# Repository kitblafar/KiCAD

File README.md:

# KiCAD
KiCAD Projetcs at Work and at home

## Includes
- Test 141: A manufacturing test board

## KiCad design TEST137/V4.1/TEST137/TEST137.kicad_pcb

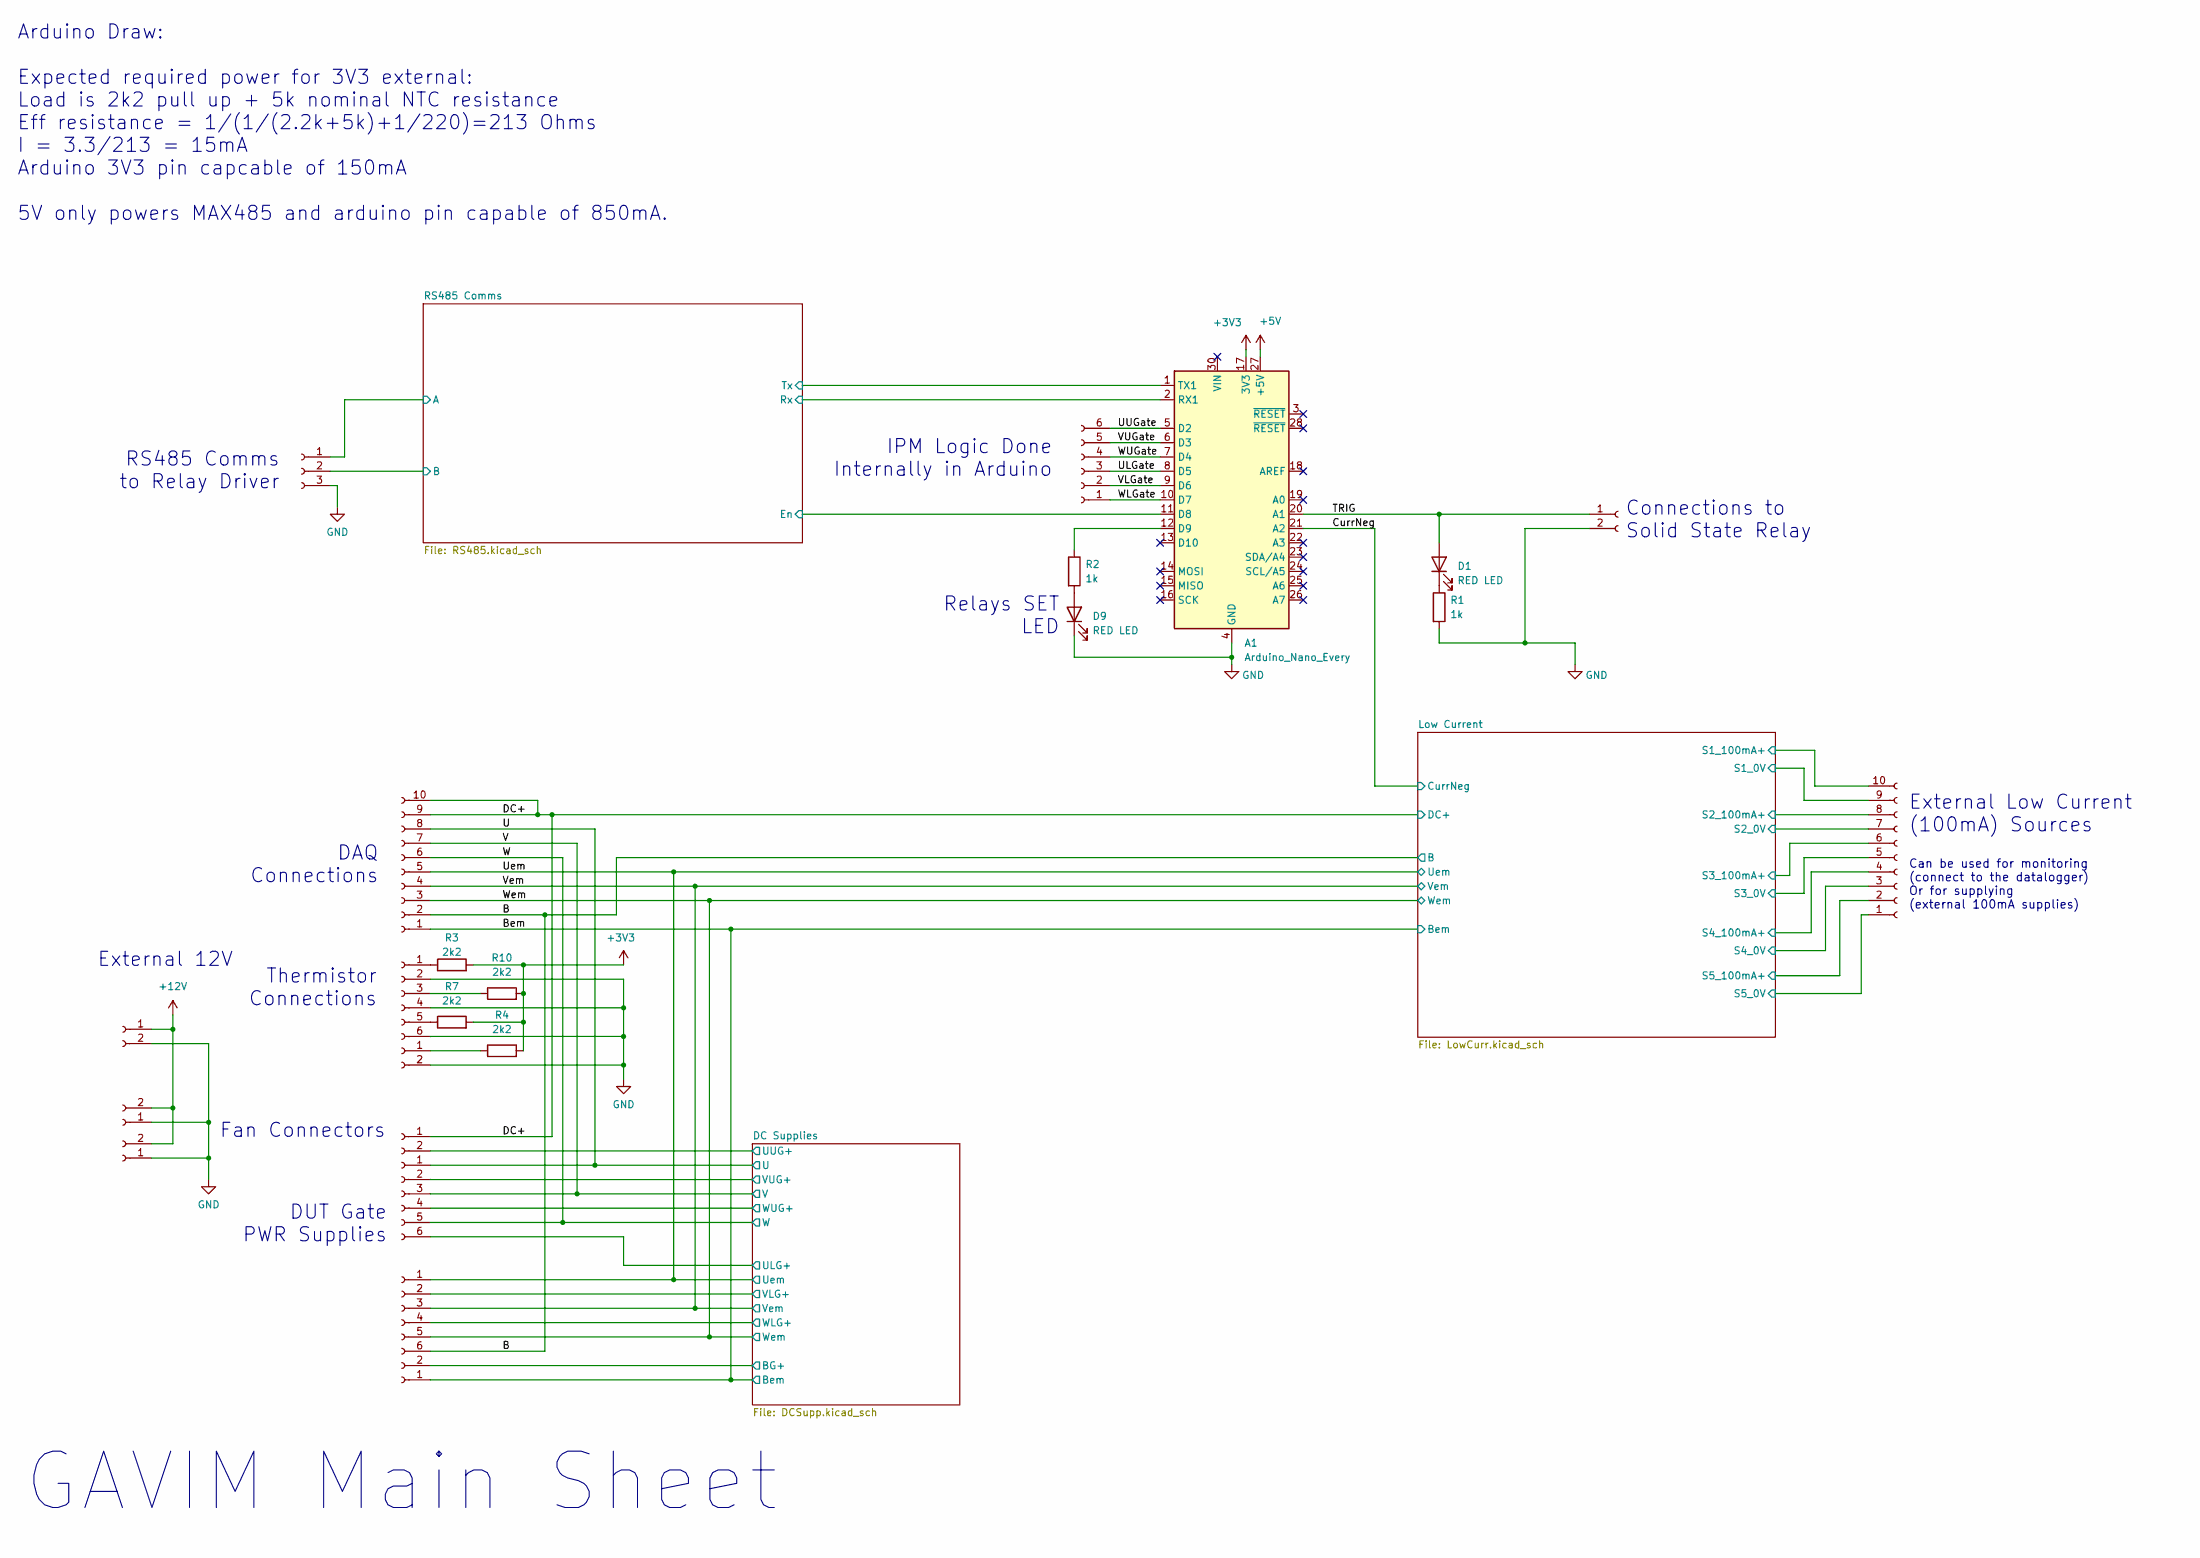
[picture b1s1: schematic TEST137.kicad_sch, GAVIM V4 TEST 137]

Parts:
A1: Arduino_Nano_Every; Arduino_Nano
D1, D9: RED LED; LED_D4.0mm
J1, J3, J4, J6: Conn_01x06_Socket; TB00150006BE
J2, J5, J11, J14: Conn_01x02_Socket; CUI_TB001-500-02BE
J7, J10: Conn_01x10_Socket; SHDR10W100P0X500_1X10_5000X900X1250P
J8, J12, J13: Conn_01x02_Socket; JST_VH_B2P-VH_1x02_P3.96mm_Vertical
J9: Conn_01x03_Socket; B3P-VH
R1, R2: 1k; R_0603_1608Metric_Pad0.98x0.95mm_HandSolder
R3, R4, R7, R10: 2k2; R_0603_1608Metric_Pad0.98x0.95mm_HandSolder

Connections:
+3V3: A1.17 (3V3), R3.2, R4.2, R7.2, R10.2
+5V: A1.27 (+5V); also elsewhere on the board
+12V: J11.1, J12.2, J13.2; also elsewhere on the board
/B: J4.6, J10.2; also elsewhere on the board
/Bem: J5.1, J10.1; also elsewhere on the board
/CurrNeg: A1.21 (A2); also elsewhere on the board
/DC Supplies/BG+: J5.2; also elsewhere on the board
/DC Supplies/ULG+: J3.6; also elsewhere on the board
/DC Supplies/UUG+: J2.2; also elsewhere on the board
/DC Supplies/VLG+: J4.2; also elsewhere on the board
/DC Supplies/VUG+: J3.2; also elsewhere on the board
/DC Supplies/WLG+: J4.4; also elsewhere on the board
/DC Supplies/WUG+: J3.4; also elsewhere on the board
/DC+: J2.1, J10.9, J10.10; also elsewhere on the board
/Low Current/S1_0V: J7.9; also elsewhere on the board
/Low Current/S1_100mA+: J7.10; also elsewhere on the board
/Low Current/S2_0V: J7.7; also elsewhere on the board
/Low Current/S2_100mA+: J7.8; also elsewhere on the board
/Low Current/S3_0V: J7.5; also elsewhere on the board
/Low Current/S3_100mA+: J7.6; also elsewhere on the board
/Low Current/S4_0V: J7.3; also elsewhere on the board
/Low Current/S4_100mA+: J7.4; also elsewhere on the board
/Low Current/S5_0V: J7.1; also elsewhere on the board
/Low Current/S5_100mA+: J7.2; also elsewhere on the board
/RS485 Comms/B+: J9.2; also elsewhere on the board
/RS485 Comms/B-: J9.1; also elsewhere on the board
/RS485 Comms/En: A1.11 (D8); also elsewhere on the board
/RS485 Comms/Rx: A1.2 (RX1); also elsewhere on the board
/RS485 Comms/Tx: A1.1 (TX1); also elsewhere on the board
/TRIG: A1.20 (A1), D1.2 (A), J8.1
/U: J3.1, J10.8; also elsewhere on the board
/ULGate: A1.8 (D5), J1.3
/UUGate: A1.5 (D2), J1.6
/Uem: J4.1, J10.5; also elsewhere on the board
/V: J3.3, J10.7; also elsewhere on the board
/VLGate: A1.9 (D6), J1.2
/VUGate: A1.6 (D3), J1.5
/Vem: J4.3, J10.4; also elsewhere on the board
/W: J3.5, J10.6; also elsewhere on the board
/WLGate: A1.10 (D7), J1.1
/WUGate: A1.7 (D4), J1.4
/Wem: J4.5, J10.3; also elsewhere on the board
GND: A1.4 (GND), A1.29 (GND), D9.1 (K), J6.2, J6.4, J6.6, J8.2, J9.3, J11.2, J12.1, J13.1, J14.2, R1.2; also elsewhere on the board
unnamed: A1.12 (D9), R2.1
unnamed: D1.1 (K), R1.1
unnamed: D9.2 (A), R2.2
unnamed: J6.1, R3.1
unnamed: J6.3, R10.1
unnamed: J6.5, R7.1
unnamed: J14.1, R4.1

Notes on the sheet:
Can be used for monitoring (connect to the datalogger) Or for supplying (external 100mA supplies)
GAVIM Main Sheet
DAQ Connections
IPM Logic Done Internally in Arduino
External 12V
Fan Connectors
RS485 Comms to Relay Driver
DUT Gate PWR Supplies
External Low Current (100mA) Sources
Arduino Draw: Expected required power for 3V3 external: Load is 2k2 pull up + 5k nominal NTC resistance Eff resistance = 1/(1/(2.2k+5k)+1/220)=213 Ohms I = 3.3/213 = 15mA Arduino 3V3 pin capcable of 150mA 5V only powers MAX485 and arduino pin capable of 850mA.
Relays SET LED
Connections to Solid State Relay
Thermistor Connections

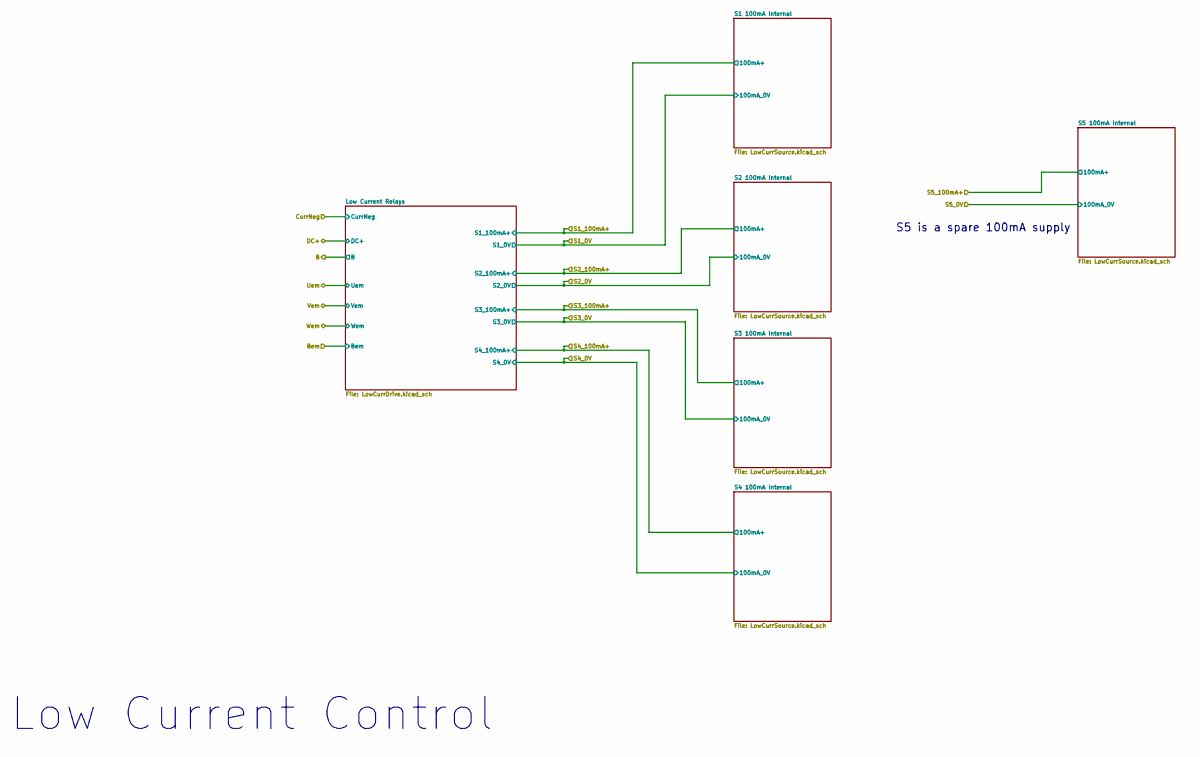
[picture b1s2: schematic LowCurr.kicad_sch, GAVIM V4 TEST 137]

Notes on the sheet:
S5 is a spare 100mA supply
Low Current Control

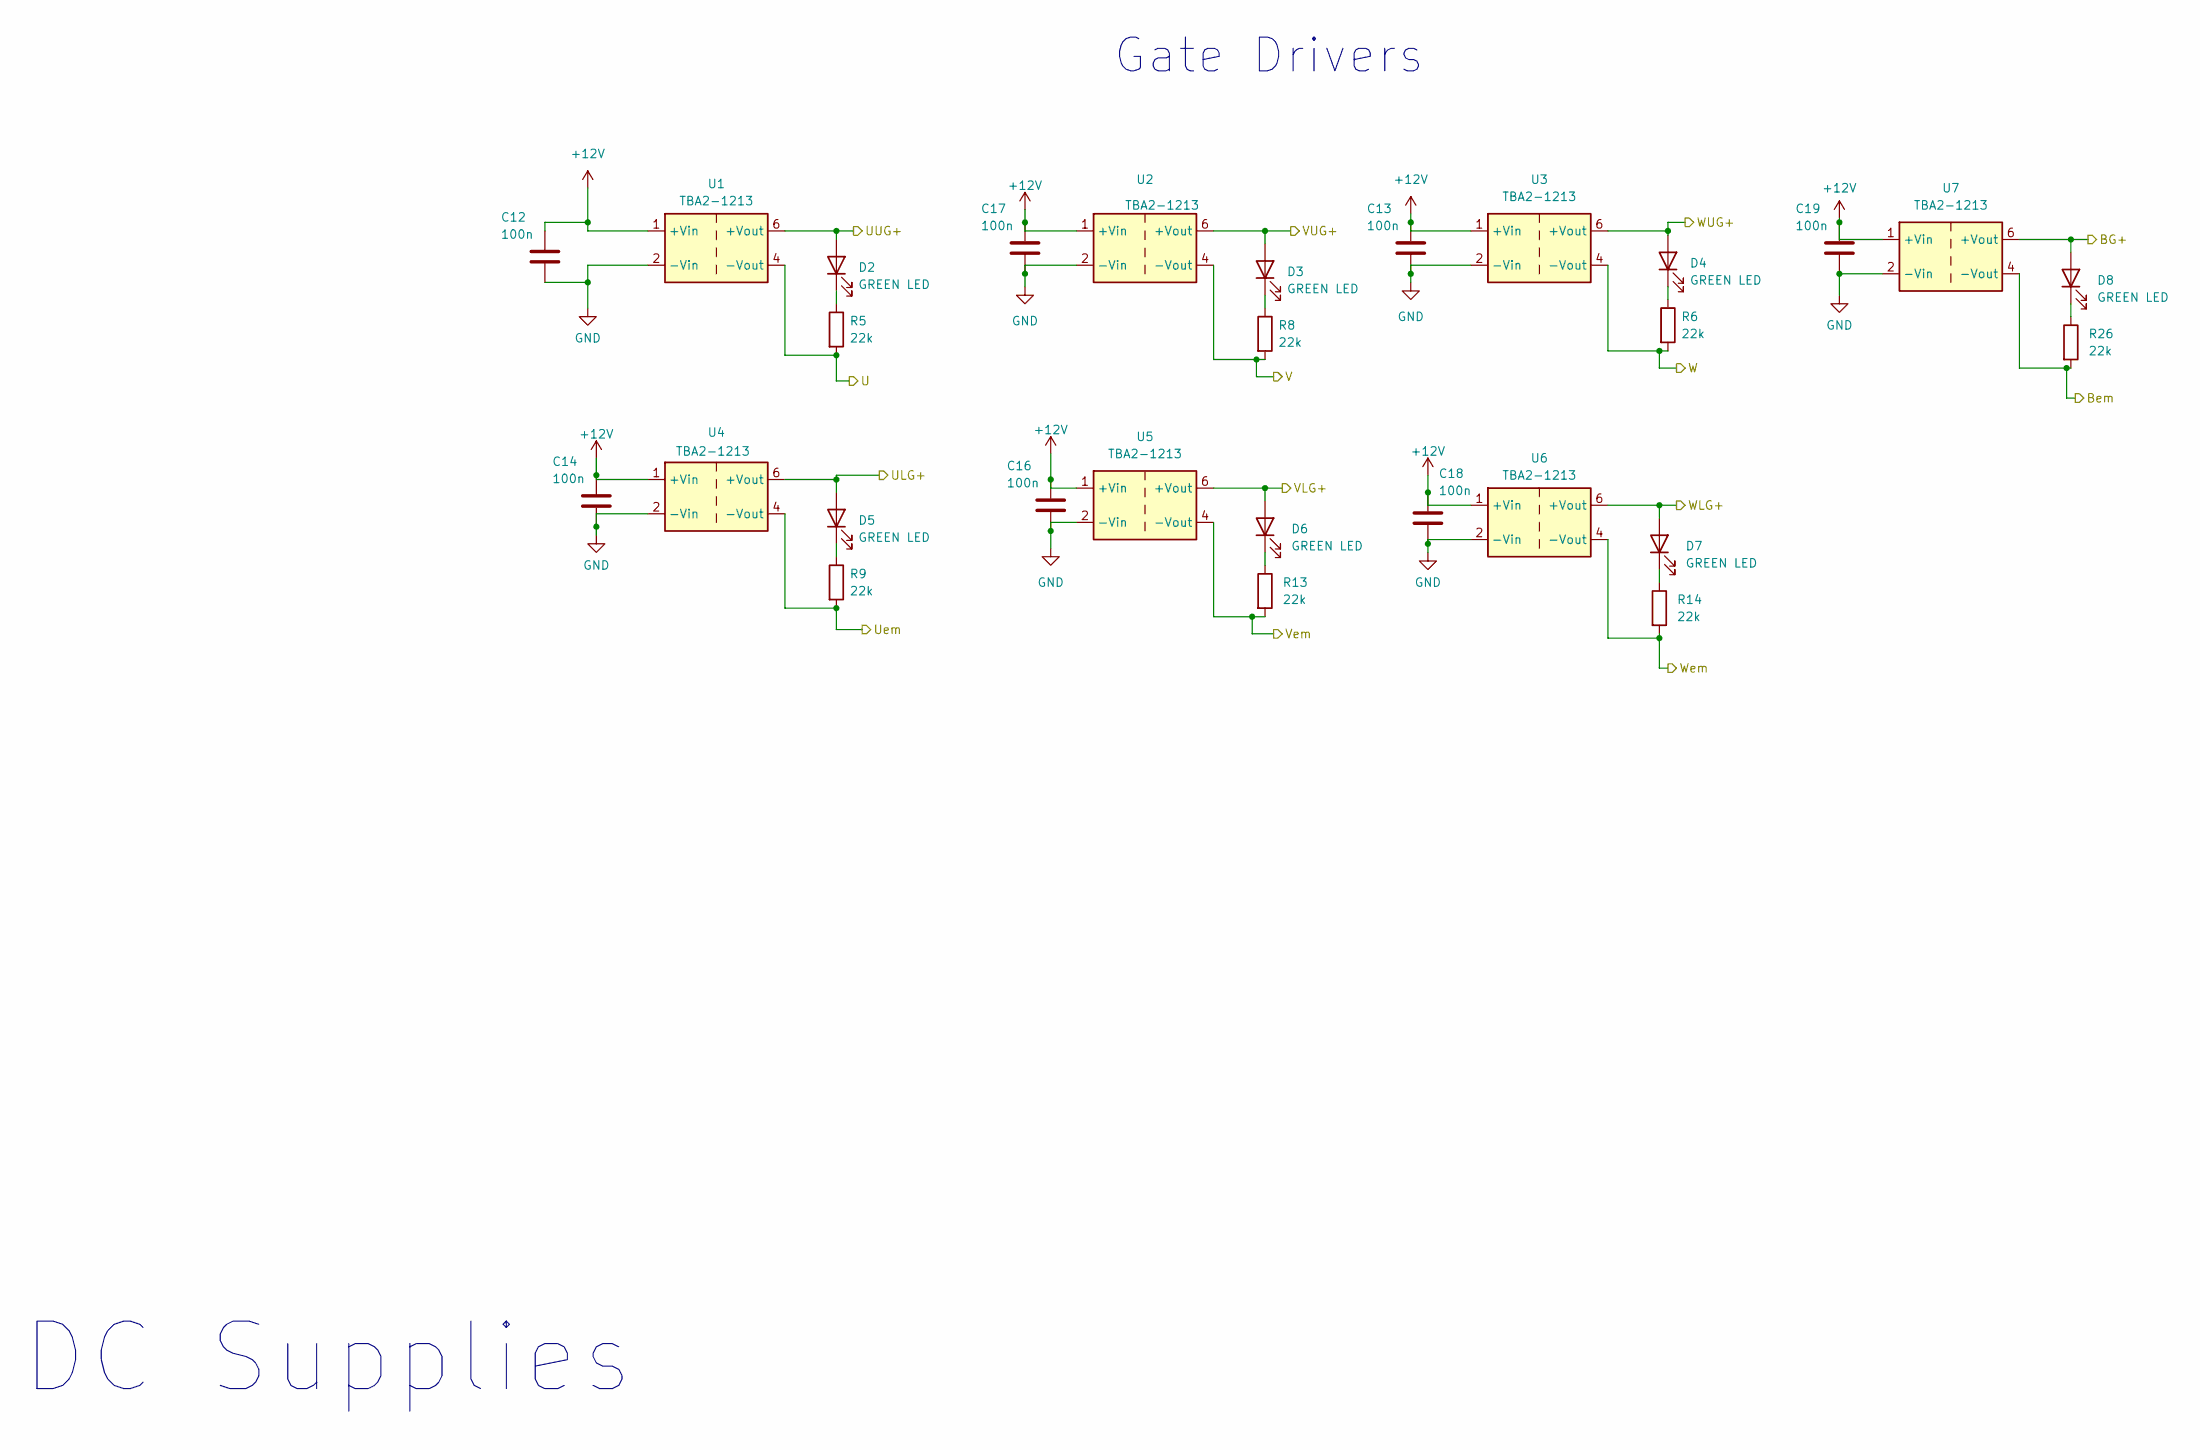
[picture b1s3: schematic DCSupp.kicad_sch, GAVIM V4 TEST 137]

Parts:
C12, C13, C14, C16, C17, C18, C19: 100n; C_0603_1608Metric_Pad1.08x0.95mm_HandSolder
D2, D3, D4, D5, D6, D7, D8: GREEN LED; LED_D4.0mm
R5, R6, R8, R9, R13, R14, R26: 22k; R_0603_1608Metric_Pad0.98x0.95mm_HandSolder
U1, U2, U3, U4, U5, U6, U7: TBA2-1213; TBA21213

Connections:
+12V: C12.1, C13.1, C14.1, C16.1, C17.1, C18.1, C19.1, U1.1 (+Vin), U2.1 (+Vin), U3.1 (+Vin), U4.1 (+Vin), U5.1 (+Vin), U6.1 (+Vin), U7.1 (+Vin); also elsewhere on the board
/Bem: R26.2, U7.4 (-Vout); also elsewhere on the board
/DC Supplies/BG+: D8.2 (A), U7.6 (+Vout); also elsewhere on the board
/DC Supplies/ULG+: D5.2 (A), U4.6 (+Vout); also elsewhere on the board
/DC Supplies/UUG+: D2.2 (A), U1.6 (+Vout); also elsewhere on the board
/DC Supplies/VLG+: D6.2 (A), U5.6 (+Vout); also elsewhere on the board
/DC Supplies/VUG+: D3.2 (A), U2.6 (+Vout); also elsewhere on the board
/DC Supplies/WLG+: D7.2 (A), U6.6 (+Vout); also elsewhere on the board
/DC Supplies/WUG+: D4.2 (A), U3.6 (+Vout); also elsewhere on the board
/U: R5.2, U1.4 (-Vout); also elsewhere on the board
/Uem: R9.2, U4.4 (-Vout); also elsewhere on the board
/V: R8.2, U2.4 (-Vout); also elsewhere on the board
/Vem: R13.2, U5.4 (-Vout); also elsewhere on the board
/W: R6.2, U3.4 (-Vout); also elsewhere on the board
/Wem: R14.2, U6.4 (-Vout); also elsewhere on the board
GND: C12.2, C13.2, C14.2, C16.2, C17.2, C18.2, C19.2, U1.2 (-Vin), U2.2 (-Vin), U3.2 (-Vin), U4.2 (-Vin), U5.2 (-Vin), U6.2 (-Vin), U7.2 (-Vin); also elsewhere on the board
unnamed: D2.1 (K), R5.1
unnamed: D3.1 (K), R8.1
unnamed: D4.1 (K), R6.1
unnamed: D5.1 (K), R9.1
unnamed: D6.1 (K), R13.1
unnamed: D7.1 (K), R14.1
unnamed: D8.1 (K), R26.1

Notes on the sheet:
Gate Drivers
DC Supplies

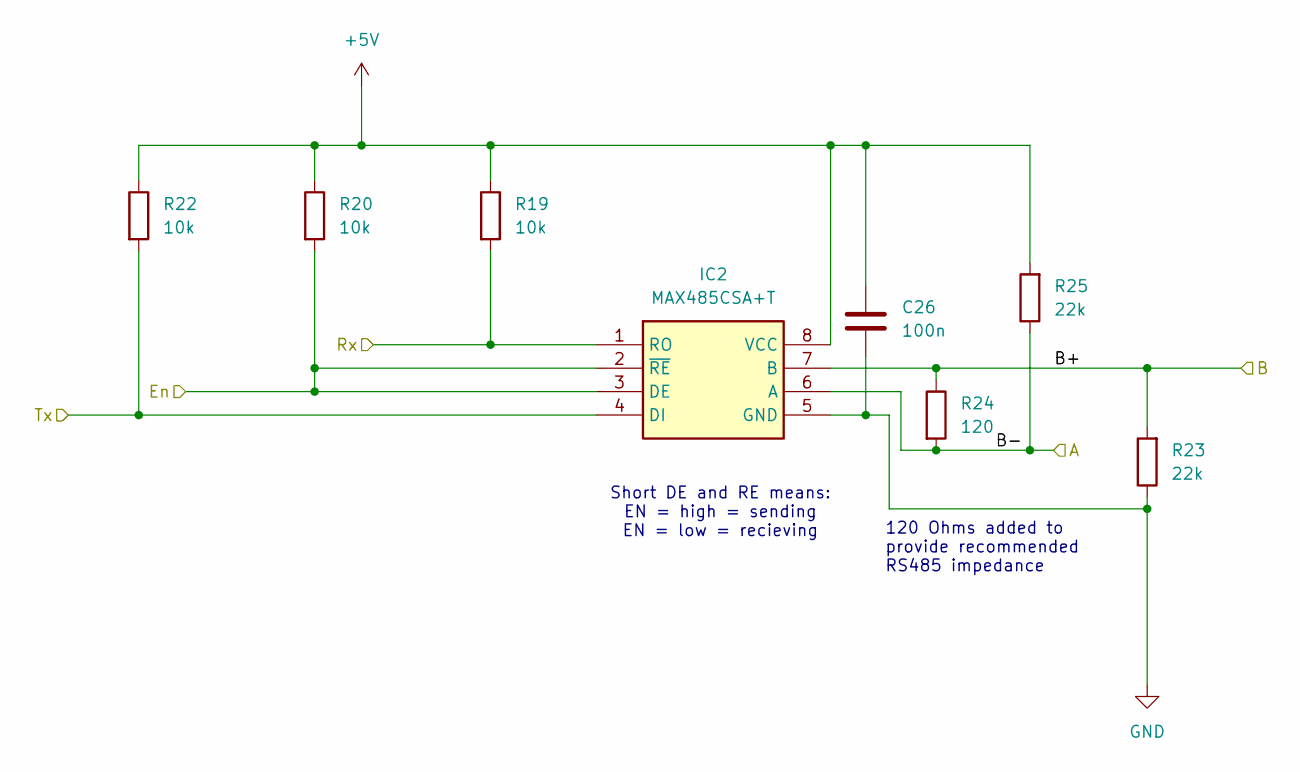
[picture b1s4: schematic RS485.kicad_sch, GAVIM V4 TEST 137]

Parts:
C26: 100n; C_0603_1608Metric_Pad1.08x0.95mm_HandSolder
IC2: MAX485CSA+T; SOIC-8_3.9x4.9mm_P1.27mm; Mouser Part Number 700-MAX485CSAT
R19, R20, R22: 10k; R_0603_1608Metric_Pad0.98x0.95mm_HandSolder
R23, R25: 22k; R_0603_1608Metric_Pad0.98x0.95mm_HandSolder
R24: 120; R_0603_1608Metric_Pad0.98x0.95mm_HandSolder

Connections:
+5V: C26.1, IC2.8 (VCC), R19.1, R20.1, R22.1, R25.2; also elsewhere on the board
/RS485 Comms/B+: IC2.7 (B), R23.2, R24.1; also elsewhere on the board
/RS485 Comms/B-: IC2.6 (A), R24.2, R25.1; also elsewhere on the board
/RS485 Comms/En: IC2.2 (~RE), IC2.3 (DE), R20.2; also elsewhere on the board
/RS485 Comms/Rx: IC2.1 (RO), R19.2; also elsewhere on the board
/RS485 Comms/Tx: IC2.4 (DI), R22.2; also elsewhere on the board
GND: C26.2, IC2.5 (GND), R23.1; also elsewhere on the board

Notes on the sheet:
Short DE and RE means: EN = high = sending EN = low = recieving
120 Ohms added to provide recommended RS485 impedance

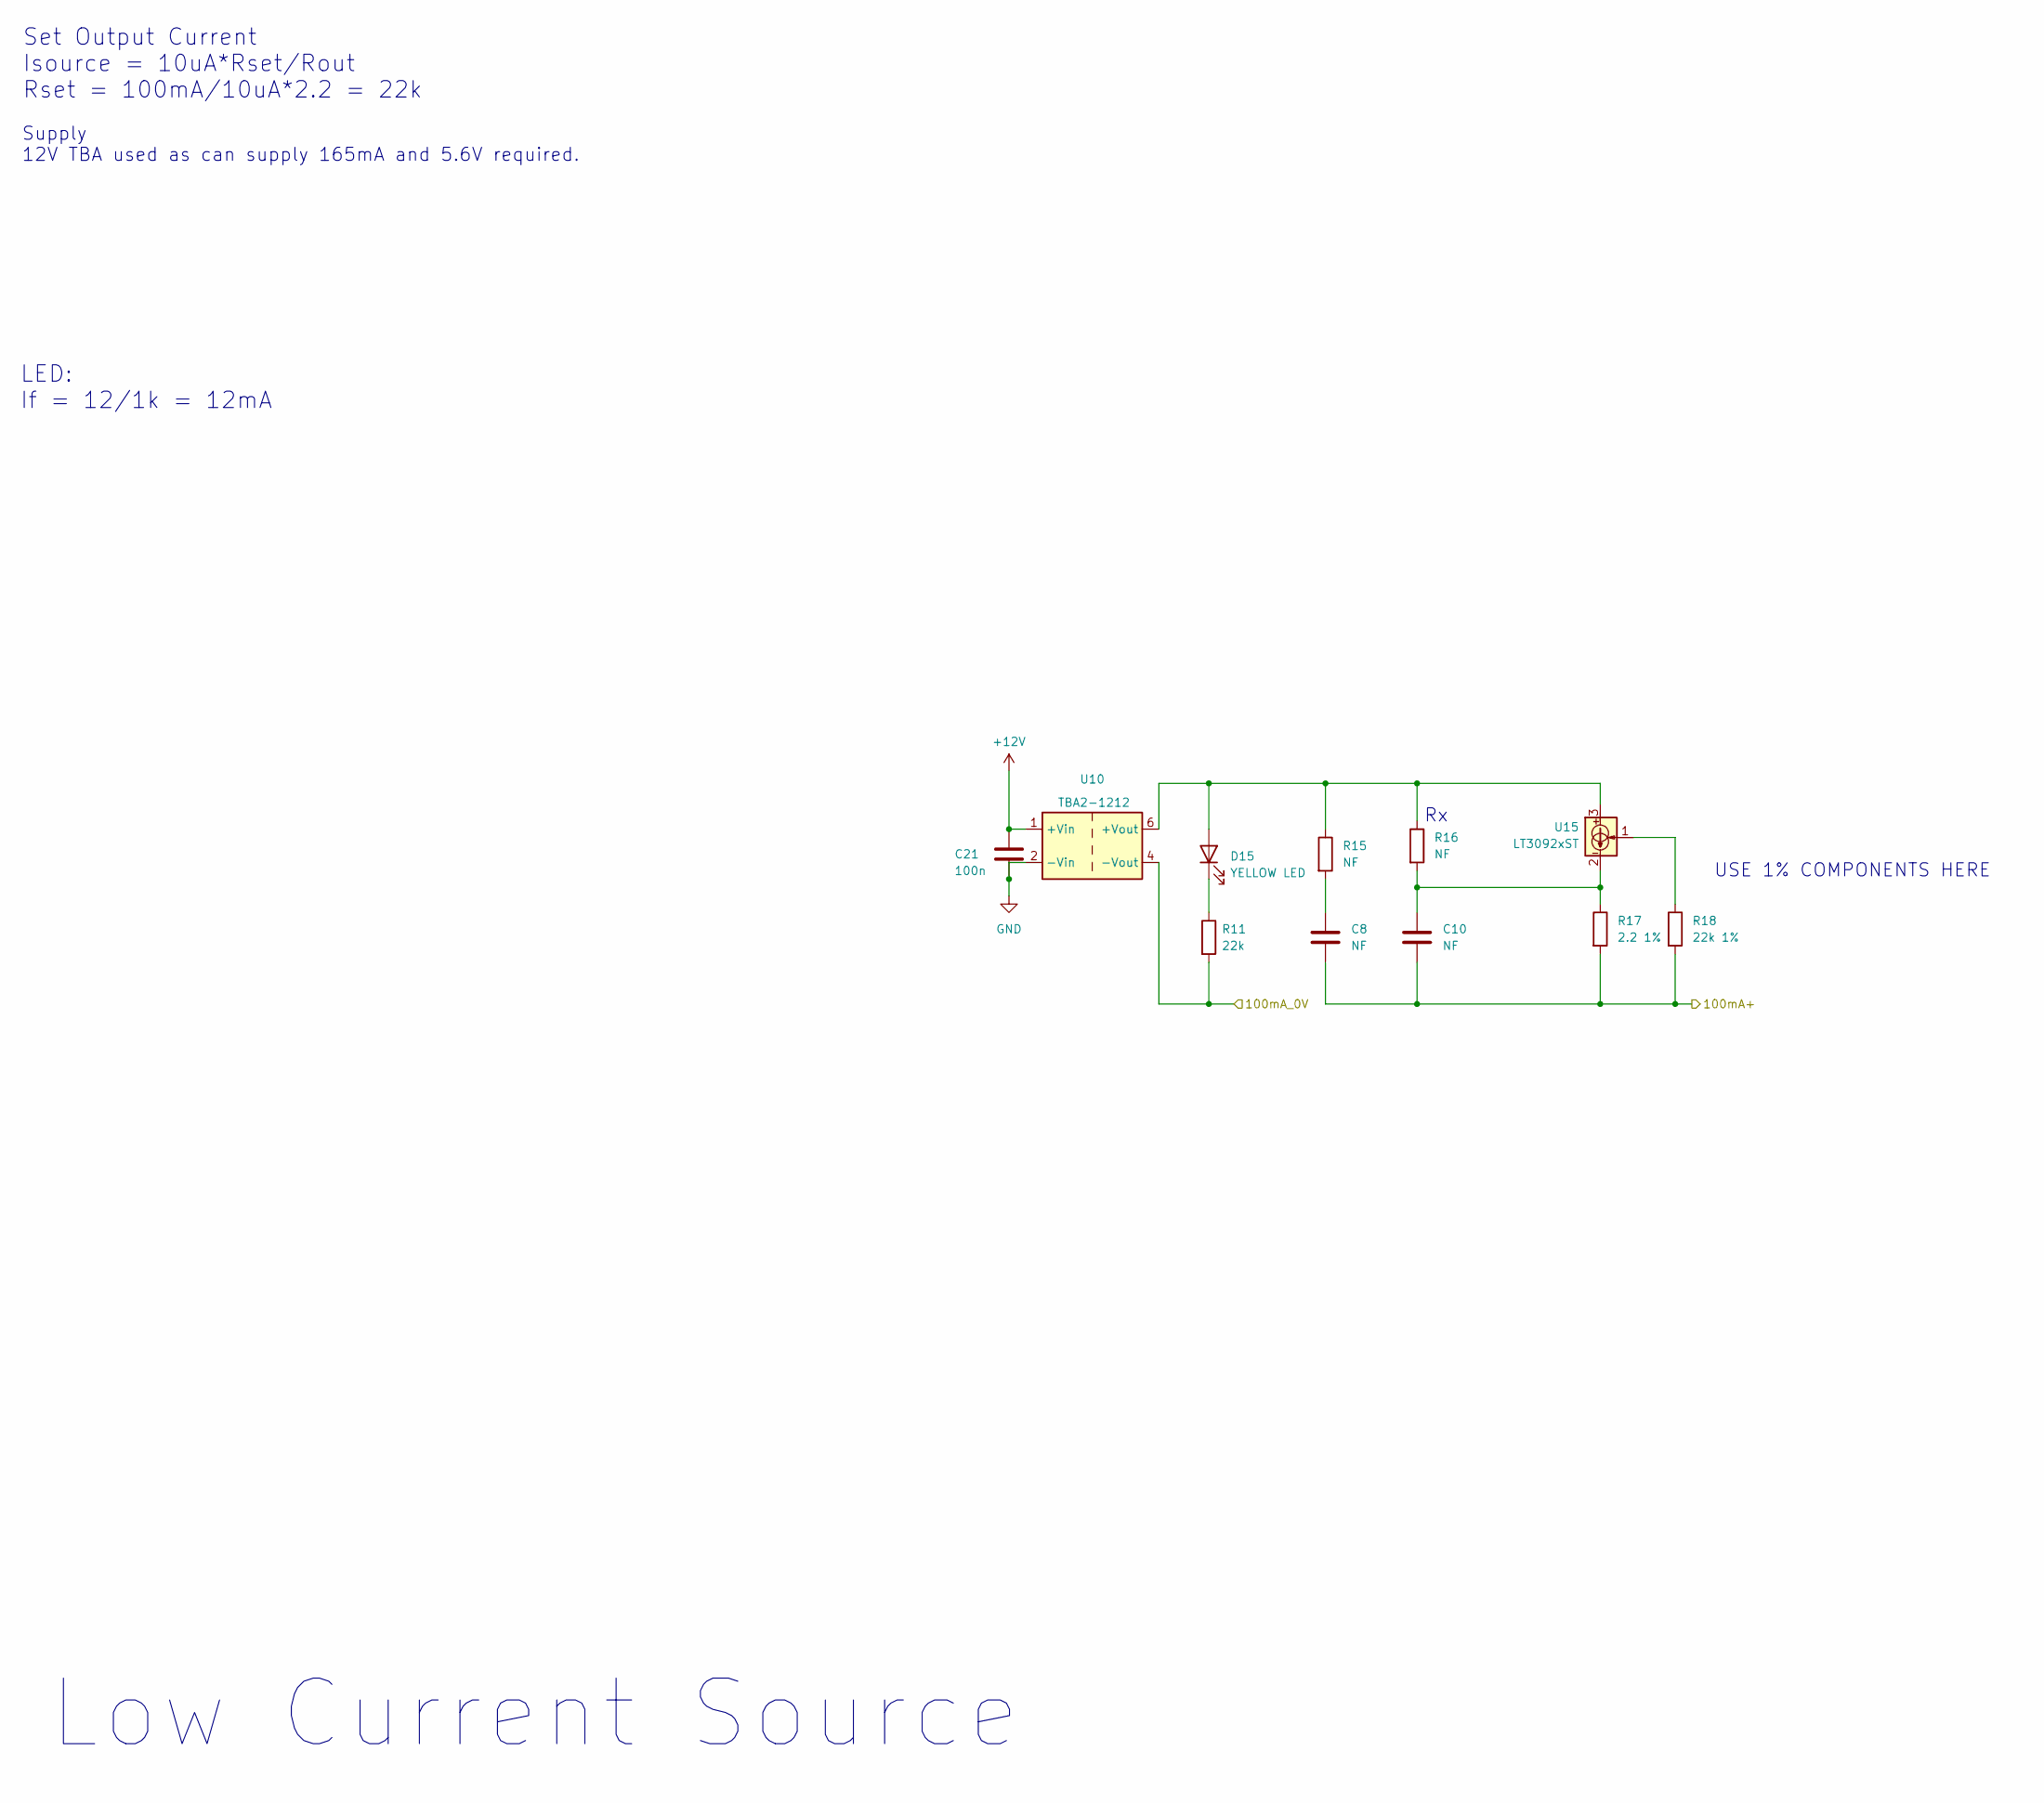
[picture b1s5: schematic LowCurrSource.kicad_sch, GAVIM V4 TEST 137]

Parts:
C8, C10: NF; C_0603_1608Metric_Pad1.08x0.95mm_HandSolder
C21: 100n; C_0603_1608Metric_Pad1.08x0.95mm_HandSolder
D15: YELLOW LED; LED_D4.0mm
R11: 22k; R_0603_1608Metric_Pad0.98x0.95mm_HandSolder
R15, R16: NF; R_0603_1608Metric_Pad0.98x0.95mm_HandSolder
R17: 2.2 1%; R_0603_1608Metric_Pad0.98x0.95mm_HandSolder
R18: 22k 1%; R_0603_1608Metric_Pad0.98x0.95mm_HandSolder
U10: TBA2-1212; TBA21213
U15: LT3092xST; SOT-223-3_TabPin2

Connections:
+12V: C21.1, U10.1 (+Vin); also elsewhere on the board
/Low Current/S5_0V: R11.2, U10.4 (-Vout); also elsewhere on the board
/Low Current/S5_100mA+: C8.2, C10.2, R17.2, R18.2; also elsewhere on the board
GND: C21.2, U10.2 (-Vin); also elsewhere on the board
unnamed: C8.1, R15.2
unnamed: C10.1, R16.2, R17.1, U15.2
unnamed: D15.2 (A), R15.1, R16.1, U10.6 (+Vout), U15.3
unnamed: D15.1 (K), R11.1
unnamed: R18.1, U15.1

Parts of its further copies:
C1, C2, C3, C4, C7, C9, C11, C15: NF; C_0603_1608Metric_Pad1.08x0.95mm_HandSolder
C22, C23, C24, C25: 100n; C_0603_1608Metric_Pad1.08x0.95mm_HandSolder
D11, D12, D13, D14: YELLOW LED; LED_D4.0mm
R27, R46, R51, R61: 22k; R_0603_1608Metric_Pad0.98x0.95mm_HandSolder
R28, R43, R47, R48, R52, R53, R62, R63: NF; R_0603_1608Metric_Pad0.98x0.95mm_HandSolder
R44, R49, R54, R64: 2.2 1%; R_0603_1608Metric_Pad0.98x0.95mm_HandSolder
R45, R50, R55, R65: 22k 1%; R_0603_1608Metric_Pad0.98x0.95mm_HandSolder
U9, U11, U12, U13: TBA2-1212; TBA21213
U18, U20, U22, U26: LT3092xST; SOT-223-3_TabPin2

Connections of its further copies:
+12V: C22.1, C23.1, C24.1, C25.1, U9.1 (+Vin), U11.1 (+Vin), U12.1 (+Vin), U13.1 (+Vin); also elsewhere on the board
/Low Current/S1_0V: R51.2, U9.4 (-Vout); also elsewhere on the board
/Low Current/S1_100mA+: C4.2, C11.2, R54.2, R55.2; also elsewhere on the board
/Low Current/S2_0V: R46.2, U11.4 (-Vout); also elsewhere on the board
/Low Current/S2_100mA+: C3.2, C9.2, R49.2, R50.2; also elsewhere on the board
/Low Current/S3_0V: R27.2, U12.4 (-Vout); also elsewhere on the board
/Low Current/S3_100mA+: C2.2, C7.2, R44.2, R45.2; also elsewhere on the board
/Low Current/S4_0V: R61.2, U13.4 (-Vout); also elsewhere on the board
/Low Current/S4_100mA+: C1.2, C15.2, R64.2, R65.2; also elsewhere on the board
GND: C22.2, C23.2, C24.2, C25.2, U9.2 (-Vin), U11.2 (-Vin), U12.2 (-Vin), U13.2 (-Vin); also elsewhere on the board
unnamed: C1.1, R63.2, R64.1, U26.2
unnamed: C2.1, R43.2, R44.1, U18.2
unnamed: C3.1, R48.2, R49.1, U20.2
unnamed: C4.1, R53.2, R54.1, U22.2
unnamed: C7.1, R28.2
unnamed: C9.1, R47.2
unnamed: C11.1, R52.2
unnamed: C15.1, R62.2
unnamed: D11.2 (A), R52.1, R53.1, U9.6 (+Vout), U22.3
unnamed: D11.1 (K), R51.1
unnamed: D12.2 (A), R47.1, R48.1, U11.6 (+Vout), U20.3
unnamed: D12.1 (K), R46.1
unnamed: D13.2 (A), R28.1, R43.1, U12.6 (+Vout), U18.3
unnamed: D13.1 (K), R27.1
unnamed: D14.2 (A), R62.1, R63.1, U13.6 (+Vout), U26.3
unnamed: D14.1 (K), R61.1
unnamed: R45.1, U18.1
unnamed: R50.1, U20.1
unnamed: R55.1, U22.1
unnamed: R65.1, U26.1

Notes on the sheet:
Supply 12V TBA used as can supply 165mA and 5.6V required.
LED: If = 12/1k = 12mA
Set Output Current Isource = 10uA*Rset/Rout Rset = 100mA/10uA*2.2 = 22k
USE 1% COMPONENTS HERE
Low Current Source

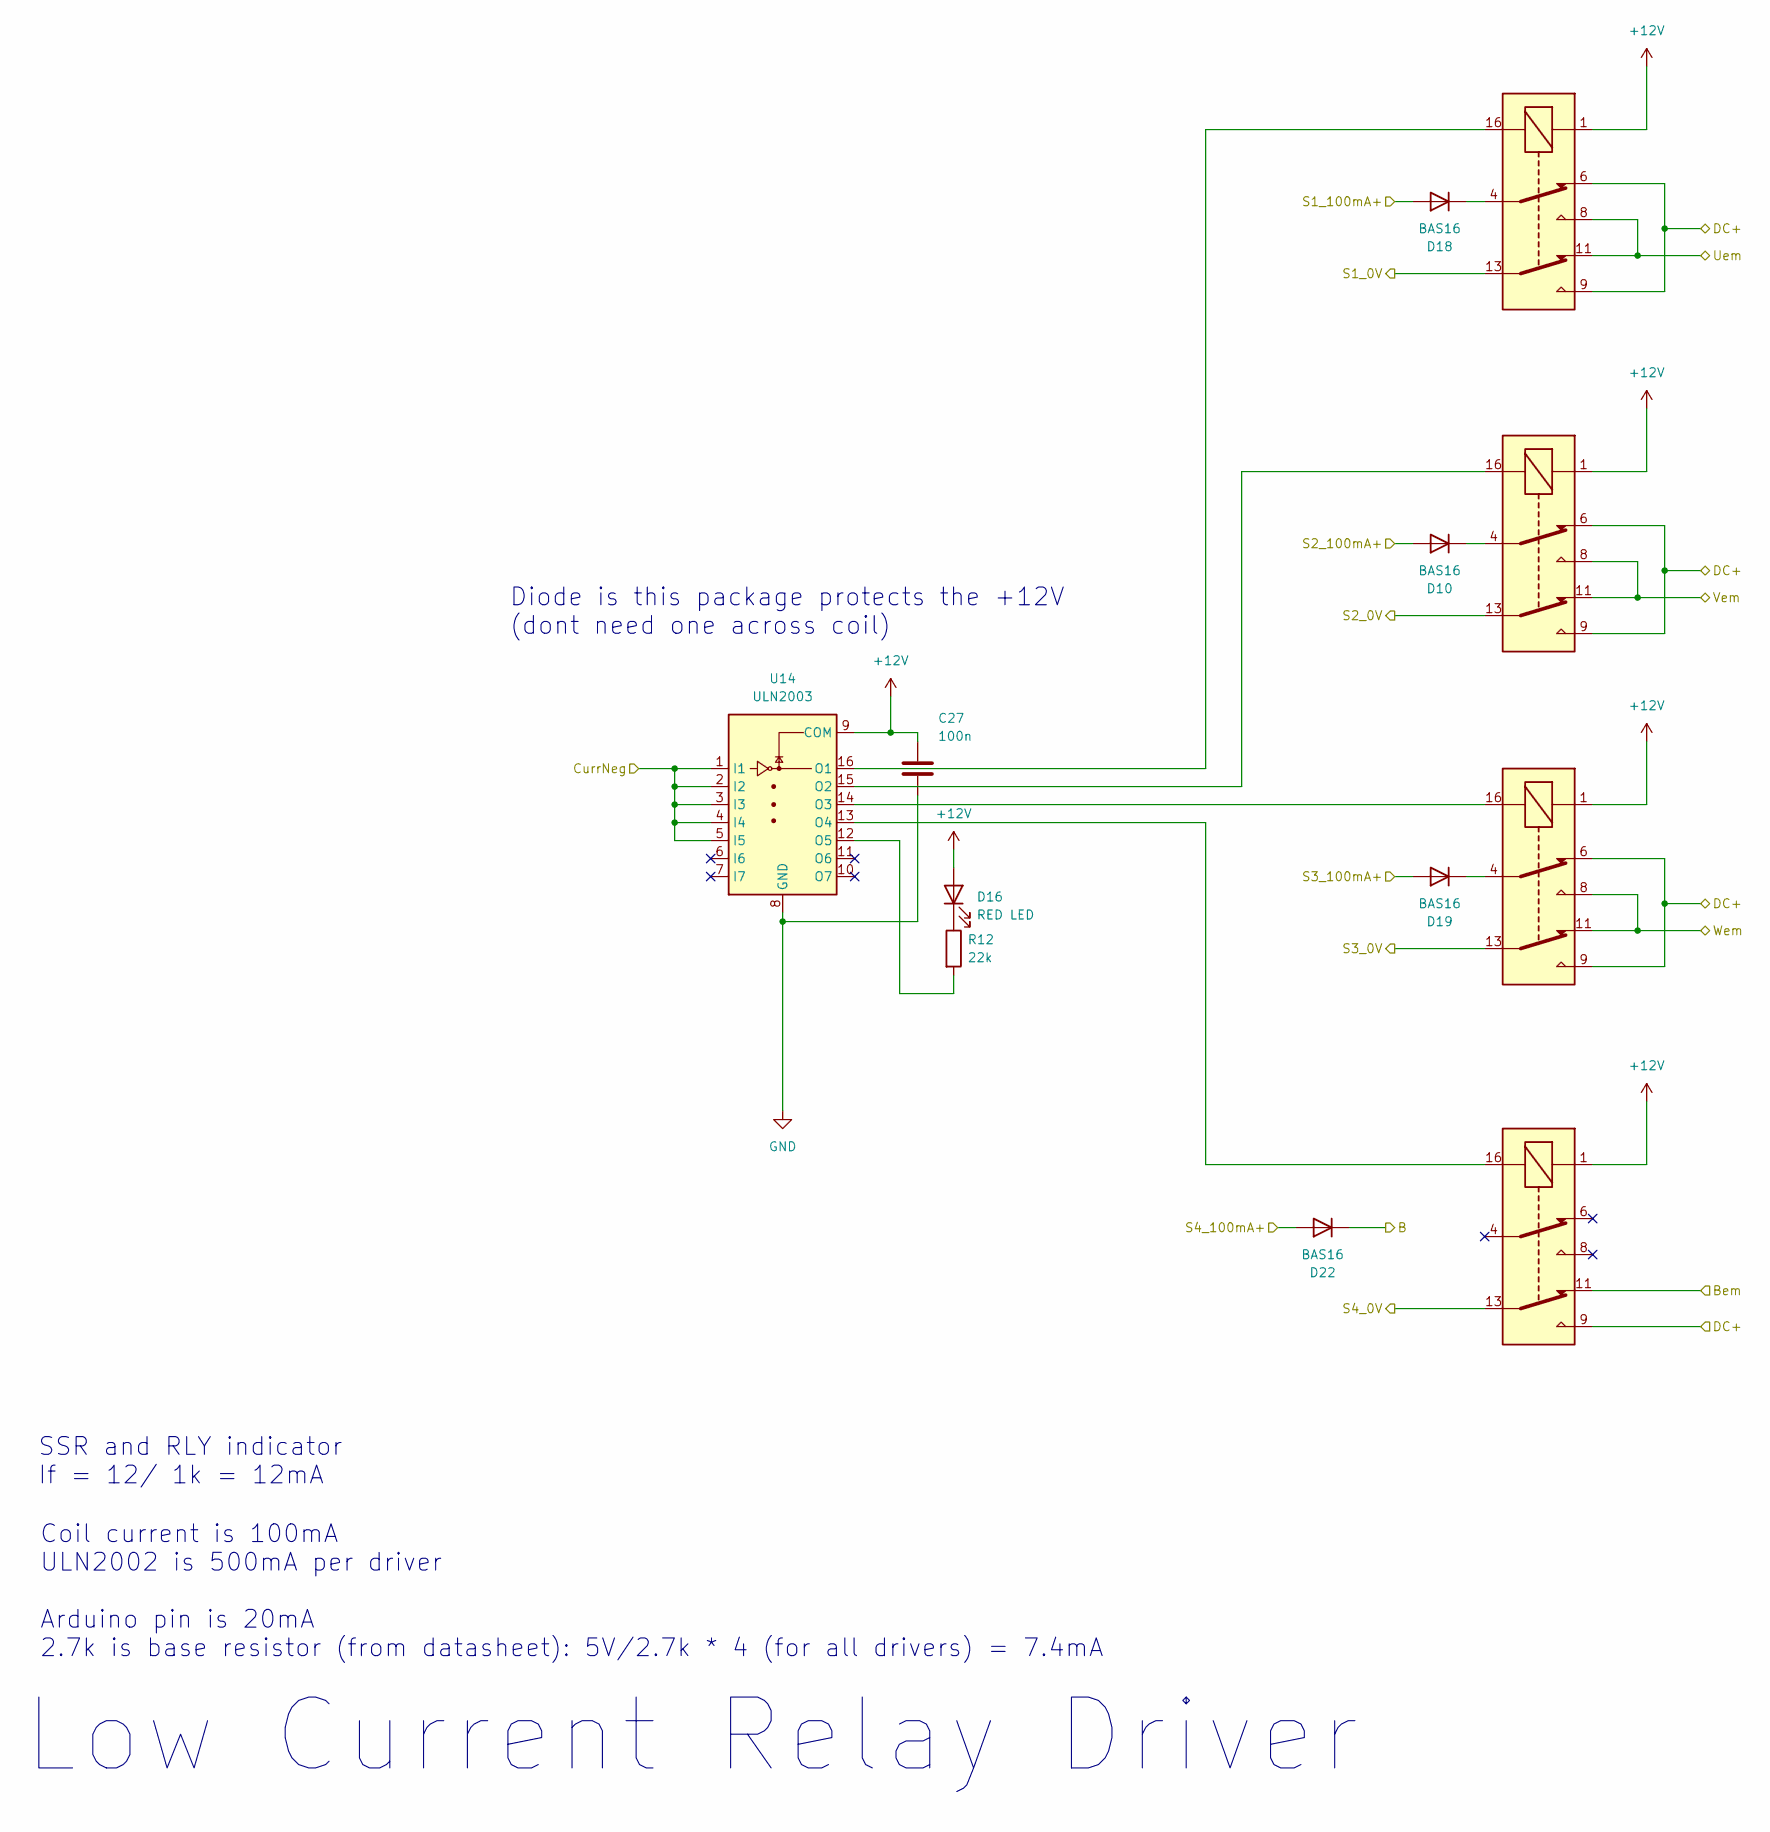
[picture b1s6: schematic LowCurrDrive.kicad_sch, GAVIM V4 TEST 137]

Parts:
C27: 100n; C_0603_1608Metric_Pad1.08x0.95mm_HandSolder
D10, D18, D19, D22: BAS16
D16: RED LED; LED_D4.0mm
K1, K2, K3, K4: G5V-2 DC12; Relay_DPDT_Omron_G5V-2
R12: 22k; R_0603_1608Metric_Pad0.98x0.95mm_HandSolder
U14: ULN2003; DIP-16_W7.62mm_LongPads

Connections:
+12V: C27.1, D16.2 (A), K1.1, K2.1, K3.1, K4.1, U14.9 (COM); also elsewhere on the board
/B: D22.1 (K); also elsewhere on the board
/Bem: K4.11; also elsewhere on the board
/CurrNeg: U14.1 (I1), U14.2 (I2), U14.3 (I3), U14.4 (I4), U14.5 (I5); also elsewhere on the board
/DC+: K1.6, K1.9, K2.6, K2.9, K3.6, K3.9, K4.9; also elsewhere on the board
/Low Current/S1_0V: K1.13; also elsewhere on the board
/Low Current/S1_100mA+: D18.2 (A); also elsewhere on the board
/Low Current/S2_0V: K2.13; also elsewhere on the board
/Low Current/S2_100mA+: D10.2 (A); also elsewhere on the board
/Low Current/S3_0V: K3.13; also elsewhere on the board
/Low Current/S3_100mA+: D19.2 (A); also elsewhere on the board
/Low Current/S4_0V: K4.13; also elsewhere on the board
/Low Current/S4_100mA+: D22.2 (A); also elsewhere on the board
/Uem: K1.8, K1.11; also elsewhere on the board
/Vem: K2.8, K2.11; also elsewhere on the board
/Wem: K3.8, K3.11; also elsewhere on the board
GND: C27.2, U14.8 (GND); also elsewhere on the board
unnamed: D10.1 (K), K2.4
unnamed: D16.1 (K), R12.1
unnamed: D18.1 (K), K1.4
unnamed: D19.1 (K), K3.4
unnamed: K1.16, U14.16 (O1)
unnamed: K2.16, U14.15 (O2)
unnamed: K3.16, U14.14 (O3)
unnamed: K4.16, U14.13 (O4)
unnamed: R12.2, U14.12 (O5)

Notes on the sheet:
Low Current Relay Driver
SSR and RLY indicator If = 12/ 1k = 12mA
Diode is this package protects the +12V (dont need one across coil)
Coil current is 100mA ULN2002 is 500mA per driver Arduino pin is 20mA 2.7k is base resistor (from datasheet): 5V/2.7k * 4 (for all drivers) = 7.4mA
